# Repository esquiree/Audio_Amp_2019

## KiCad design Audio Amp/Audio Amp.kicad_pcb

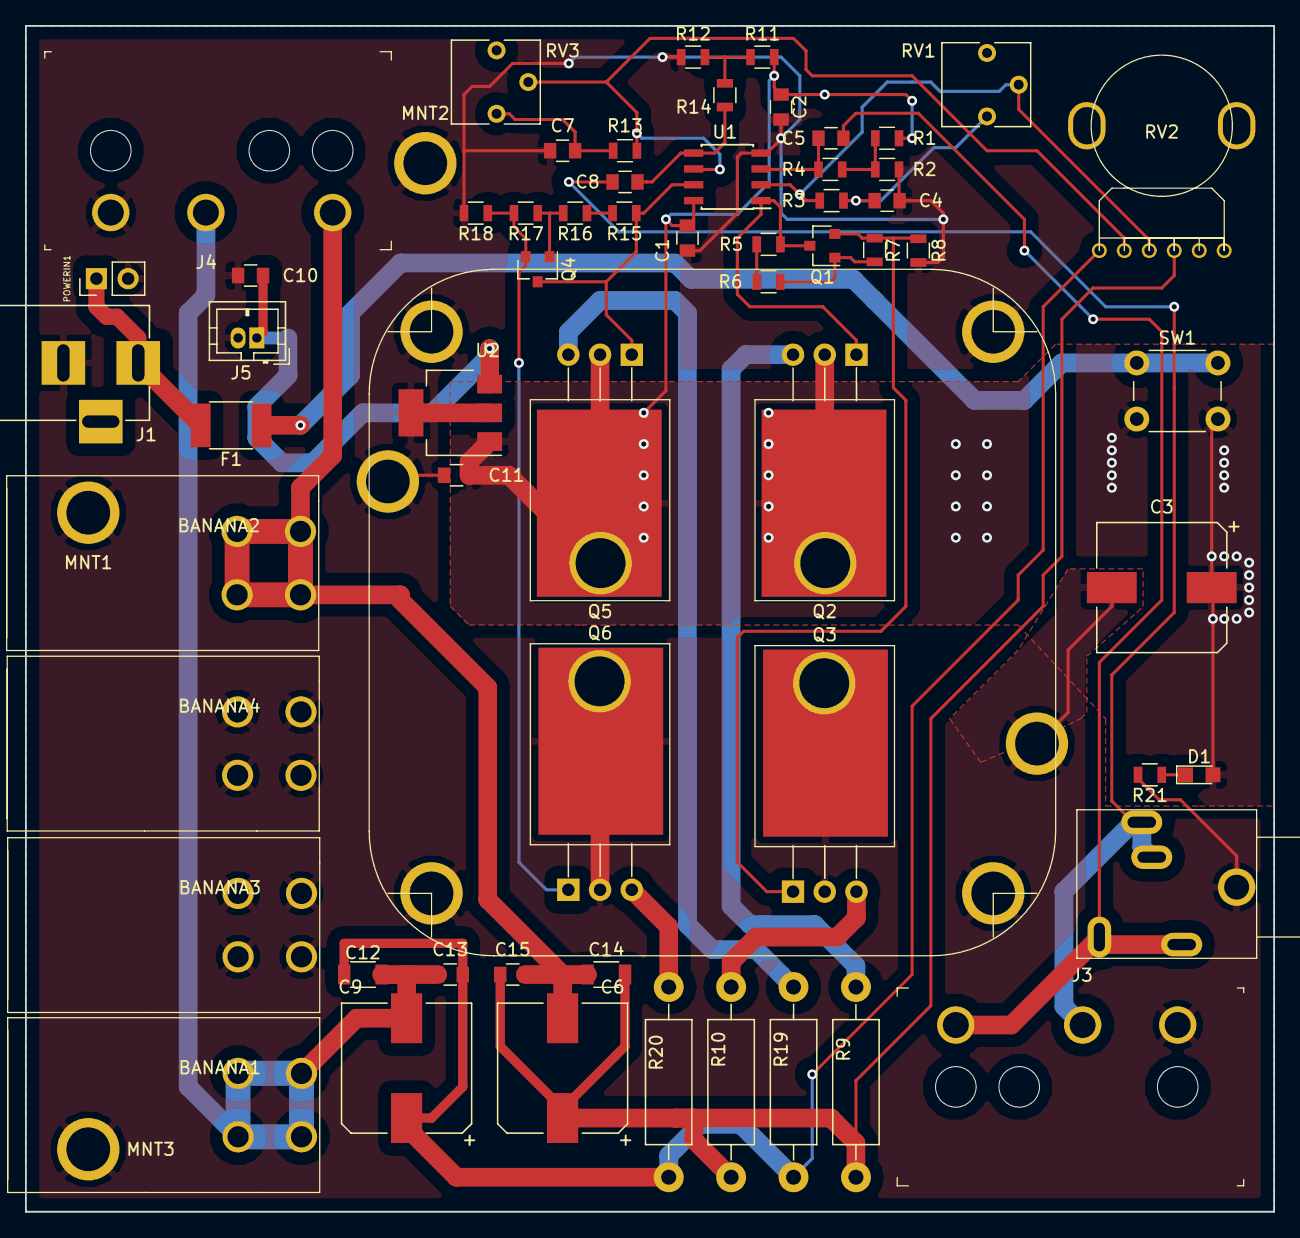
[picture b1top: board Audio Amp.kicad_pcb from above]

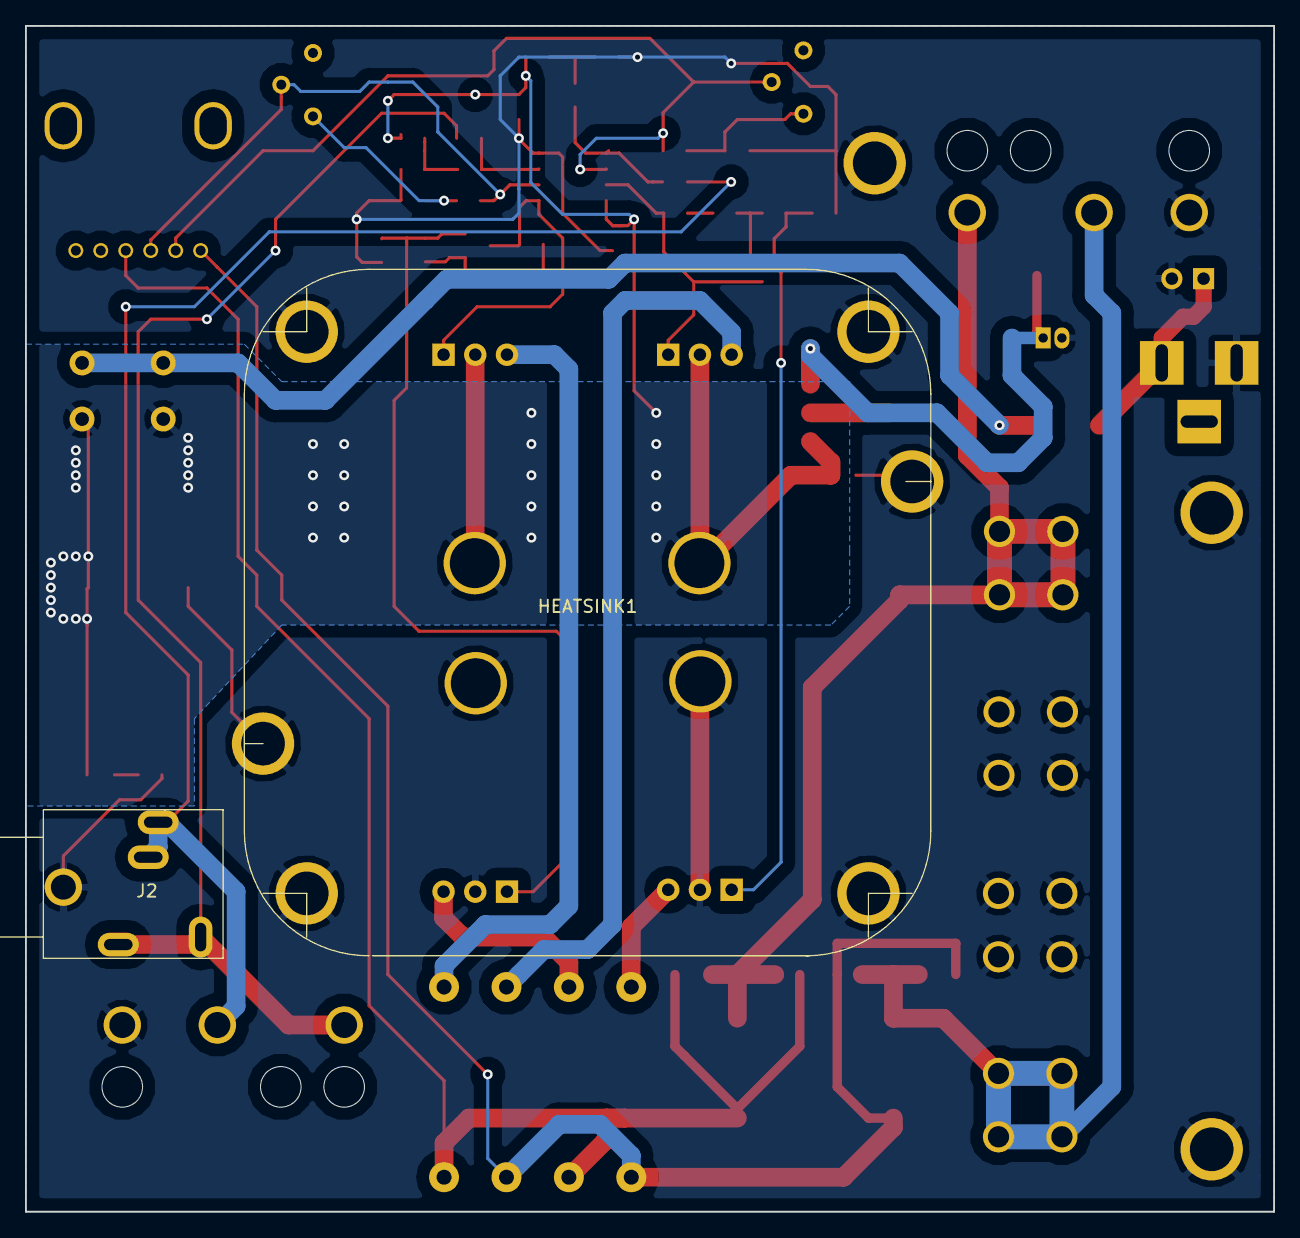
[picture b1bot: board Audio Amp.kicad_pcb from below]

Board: 2 copper layers, 100.0 x 95.0 mm, 64 parts (2 on the bottom side), 32 nets.

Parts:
BANANA1, BANANA2, BANANA3, BANANA4: Conn_01x01; Banana_RA_FULL_Plug
C1, C2, C4, C5, C7, C8, C10, C11, C13, C15: 1uF; C_0805
C3, C6, C9: 680uF; CP_Elec_10x10.5
C12, C14: 1uF; C_1206
D1: LED; LED_0805
F1: Fuse; R_1812
HEATSINK1: Conn_01x01; 55mm_heatsink
J1: Barrel_Jack; BARREL_JACK
J2: AudioJack3_Ground; Audio_5_Pin
J3, J4: AudioJack3_Ground; Headphone_Jack_6.35mm_SN49B12B
J5: Conn_01x02; JST_PH_B2B-PH-K_02x1.5.00mm_Straight
MNT1, MNT2, MNT3: Conn_01x01; 4mm Mount
POWERIN1: Conn_01x01; Pin_Header_Straight_1x02_Pitch2.54mm
Q1, Q4: Q_NPN_BEC; SOT-23
Q2, Q5: TIP120; TO-220-3_Horizontal_SOLDERTAB
Q3, Q6: TIP125; TO-220-3_Horizontal_SOLDERTAB
R1, R2, R11, R12, R21: 10K; R_0805
R3, R13: 5K; R_0805
R4, R14: 50K; R_0805
R5, R6, R7, R8, R15, R16, R17, R18: 1K; R_0805
R9, R10, R19, R20: 5; R_Axial_DIN0411_L9.9mm_D3.6mm_P15.24mm_Horizontal
RV1, RV3: R_POT; Potentiometer_Trimmer_Vishay_T73YP_Horizontal
RV2: R_POT_Dual_Separate; P120KGP
SW1: SW_SPST; SW_PUSH_6mm
U1: LM358; SOIC-8_3.9x4.9mm_Pitch1.27mm
U2: L7812; SOT-223-3_TabPin2

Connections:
+12V: C1.1, C2.1, C3.1, C11.2, D1.2, Q2.2, Q5.2, R1.1, R11.1, SW1.2, U1.8, U2.1
CHANNEL_A: C5.2, J2.3, J3.T
CHANNEL_B: C8.2, J2.2, J3.R
GND: BANANA3.1, BANANA4.1, C1.2, C2.2, C3.2, C4.2, C7.2, C10.1, C11.1, HEATSINK1.1, HEATSINK1.2, HEATSINK1.3, J1.2, J2.1, J3.S, J4.S, J5.2, MNT1.1, MNT2.1, MNT3.1, POWERIN1.2, Q3.2, Q6.2, R2.2, R8.2, R12.2, R18.2, R21.2, U1.4, U2.2
unnamed: C4.1, R3.2, RV1.1
unnamed: C5.1, R4.2, U1.3
unnamed: C7.1, R13.2, RV3.1
unnamed: C8.1, R14.2, U1.5
unnamed: C10.2, J5.1, U2.3
unnamed: C9.1, C12.1, C13.1, R19.2, R20.1, RV2.2
unnamed: C6.1, C14.1, C15.1, R9.2, R10.1, RV2.5
unnamed: D1.1, R21.1
unnamed: F1.1, SW1.1
unnamed: F1.2, J1.1, POWERIN1.1
unnamed: Q1.1, R6.2, R7.1
unnamed: Q1.2, Q3.1, R7.2, R8.1
unnamed: Q1.3, Q2.1, R5.1, U1.1
unnamed: Q2.3, R9.1
unnamed: Q3.3, R10.2
unnamed: Q4.1, R16.2, R17.1
unnamed: Q4.2, Q6.1, R17.2, R18.1
unnamed: Q4.3, Q5.1, R15.1, U1.7
unnamed: Q5.3, R19.1
unnamed: Q6.3, R20.2
unnamed: R1.2, R2.1, R4.1
unnamed: R3.1, RV1.2, RV2.4, U1.2
unnamed: R5.2, R6.1
unnamed: R11.2, R12.1, R14.1
unnamed: R13.1, RV2.1, RV3.2, U1.6
unnamed: R15.2, R16.1
OUTPUT_A: BANANA2.1, C6.2, C14.2, C15.2, J4.T
OUTPUT_B: BANANA1.1, C9.2, C12.2, C13.2, J4.R

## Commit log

2019-12-07 initial push rev 1.0
